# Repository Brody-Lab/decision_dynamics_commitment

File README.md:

# decision_dynamics_commitment
Code and data accompanying: Luo*, Kim*, et al. (2025). Transitions in dynamical regime and neural mode underlie perceptual decision-making. PMID: 37904994

The repository is organized into three main directories:

* `code/`: Analysis scripts and figure generation code, organized by figure.

* `data/`: Processed data files required to reproduce the analyses and figures, along with a link to the Dryad repository housing the raw data

* `figures/`: Editable vector graphics source files for the final figures.

Code and instructions for running the multi-mode drift-diffusion model (MMMDDM) can be found at https://github.com/Brody-Lab/fhmddm

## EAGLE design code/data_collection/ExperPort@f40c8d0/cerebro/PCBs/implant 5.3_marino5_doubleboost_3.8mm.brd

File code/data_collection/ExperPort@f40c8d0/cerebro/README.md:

# cerebro

Additional information and files can also be found in the Brody lab drive folder here https://drive.google.com/open?id=1JbdV_HZKmJ5FLsfGsrmhX1CqyznP0Qs2

Currently this lives in Research > Emily Dennis > cerebro

There's also a few spare files, especially the PCBs, that live in bucket in brodylab > cerebro

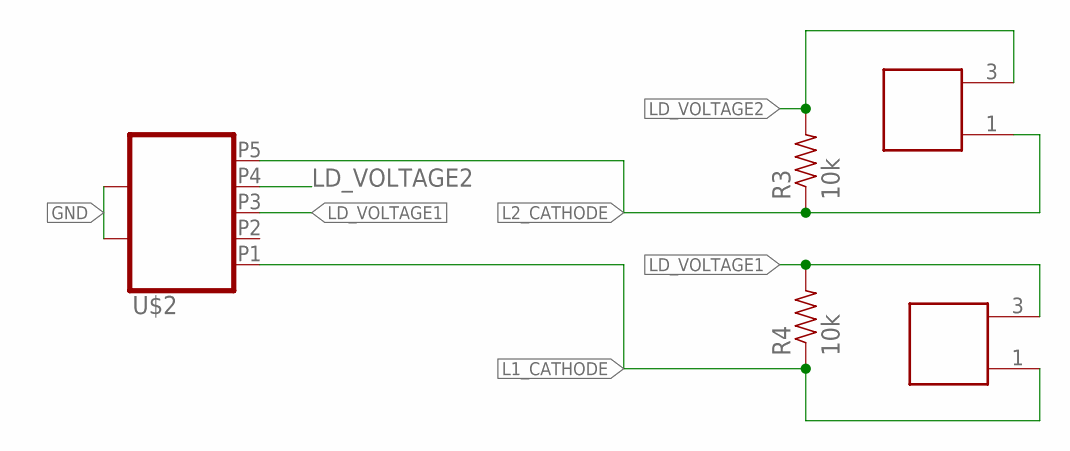
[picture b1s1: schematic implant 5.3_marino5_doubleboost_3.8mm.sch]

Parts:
R3, R4: 10k; 0805
U$2: USB_MICRO_SOCKET_VERT; USB_VERT_MICRO_SMD
U$4, U$5: TEST1; LASERDIODE_3.8_NEW

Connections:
GND: U$2.P$1, U$2.P$2, U$2.P$3
L1_CATHODE: R4.1, U$2.P1, U$5.1
L2_CATHODE: R3.1, U$2.P5, U$4.1
LD_VOLTAGE1: R4.2, U$2.P3, U$5.3
LD_VOLTAGE2: R3.2, U$2.P4, U$4.3

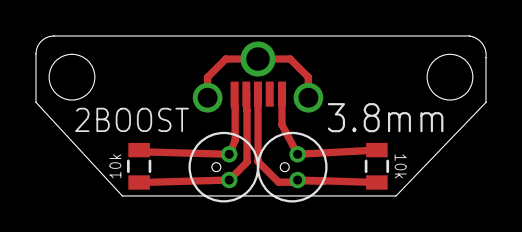
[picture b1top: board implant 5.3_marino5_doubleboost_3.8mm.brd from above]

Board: 2 copper layers, 25.0 x 8.9 mm, 5 parts (0 on the bottom side), 5 nets.

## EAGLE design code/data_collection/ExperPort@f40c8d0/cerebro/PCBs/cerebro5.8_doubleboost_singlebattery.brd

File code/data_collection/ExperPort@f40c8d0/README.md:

# ExperPort
All the code for BControl and running the Rodent Training Facility

# Setting up at home
The following are instructions for setting up at home. These are enough to start Dispatcher up, open a protocol, and be able to load and view data files.  They are not yet enough for being able to *run* and test a protocol at home. As of May 2022, these instructions work for Matlab 2022a.

1. Clone the https://github.com/Brody-Lab/ExperPort repository. 
* Note: cloning the repository to a folder in a mapped network drive, rather than to a folder in a local drive, may cause `bdata` to fail. 
3. To connect to `bdata` (one way to interact with the mySQL databases, and the way the rigs do it) you simply need to have the MySQLUtility subfolder in the ExperPort repo in your path and run `bdata_connect` to initialize the connection. This should be platform- and version-independent! If you do not intend to start Dispatcher or work with protocols and data/settings files you can stop here. Otherwise continue.
4. Clone the https://github.com/Brody-Lab/Protocols repository
5. Copy `ExperPort/Settings/Settings_Default.conf` to `ExperPort/Settings/Settings_Custom.conf`
6. In the new `Settings_Custom.conf`,
  * Edit this line to put in the path to your ExperPort directory, as in this example:
  * `GENERAL; Main_Code_Directory; /Users/carlos/Github/ExperPort`
  * Edit this line to put in the path to your SoloData directory, as in this example:
  * `GENERAL; Main_Code_Directory; /Users/carlos/Github/SoloData`
  * Edit this line to put in the path to the Protocols repository that sits outside ExperPort, as in this example:
  * `GENERAL; Protocols_Directory; ./Protocols:../Protocols`
  * Edit this line to tell it to use a local host sound server, as in this example:
  * `RIGS; sound_machine_server;     localhost;`
  * Edit this line, if needed, to make sure it says fake_rp-Box 3, for the Matlab emulator:
  * `RIGS; fake_rp_box;          3;`
1. Comment out these two lines in `mystartup.m`

   `% addpath([pwd filesep 'Protocols' filesep 'NewParamTester'])`
   
   `% addpath([pwd filesep 'Protocols' filesep 'SigmoidSamp7'])`
8. VPN into Princeton. If you forget to do this, Matlab will hang when trying to connext to bdata, and you might have to kill Matlab and start it again.
9. Start up Matlab, and change directory to wherever you cloned ExperPort
10. Run this within Matlab:  `addpath Protocols/; addpath MySQLUtility/ ; addpath Utility/ ; addpath Utility/Zut`
11. Run this within Matlab: `mystartup; newstartup; dispatcher init`
12. you're good to go, you can load a Protocol either through the menu on the Dispatcher window, or by running, in Matlab,
  `dispatcher set_protocol PROTOCOL_NAME` where `PROTOCOL_NAME` might be something like `PWM`, for example (no @ sign preceding it.
13. To load a data file after you've started a protocol, click on the green "Load Data" button in the protocol window. If needed, in the window that comes up, click on "options" at the bottom left, to ungray-out your data file and make it loadable.

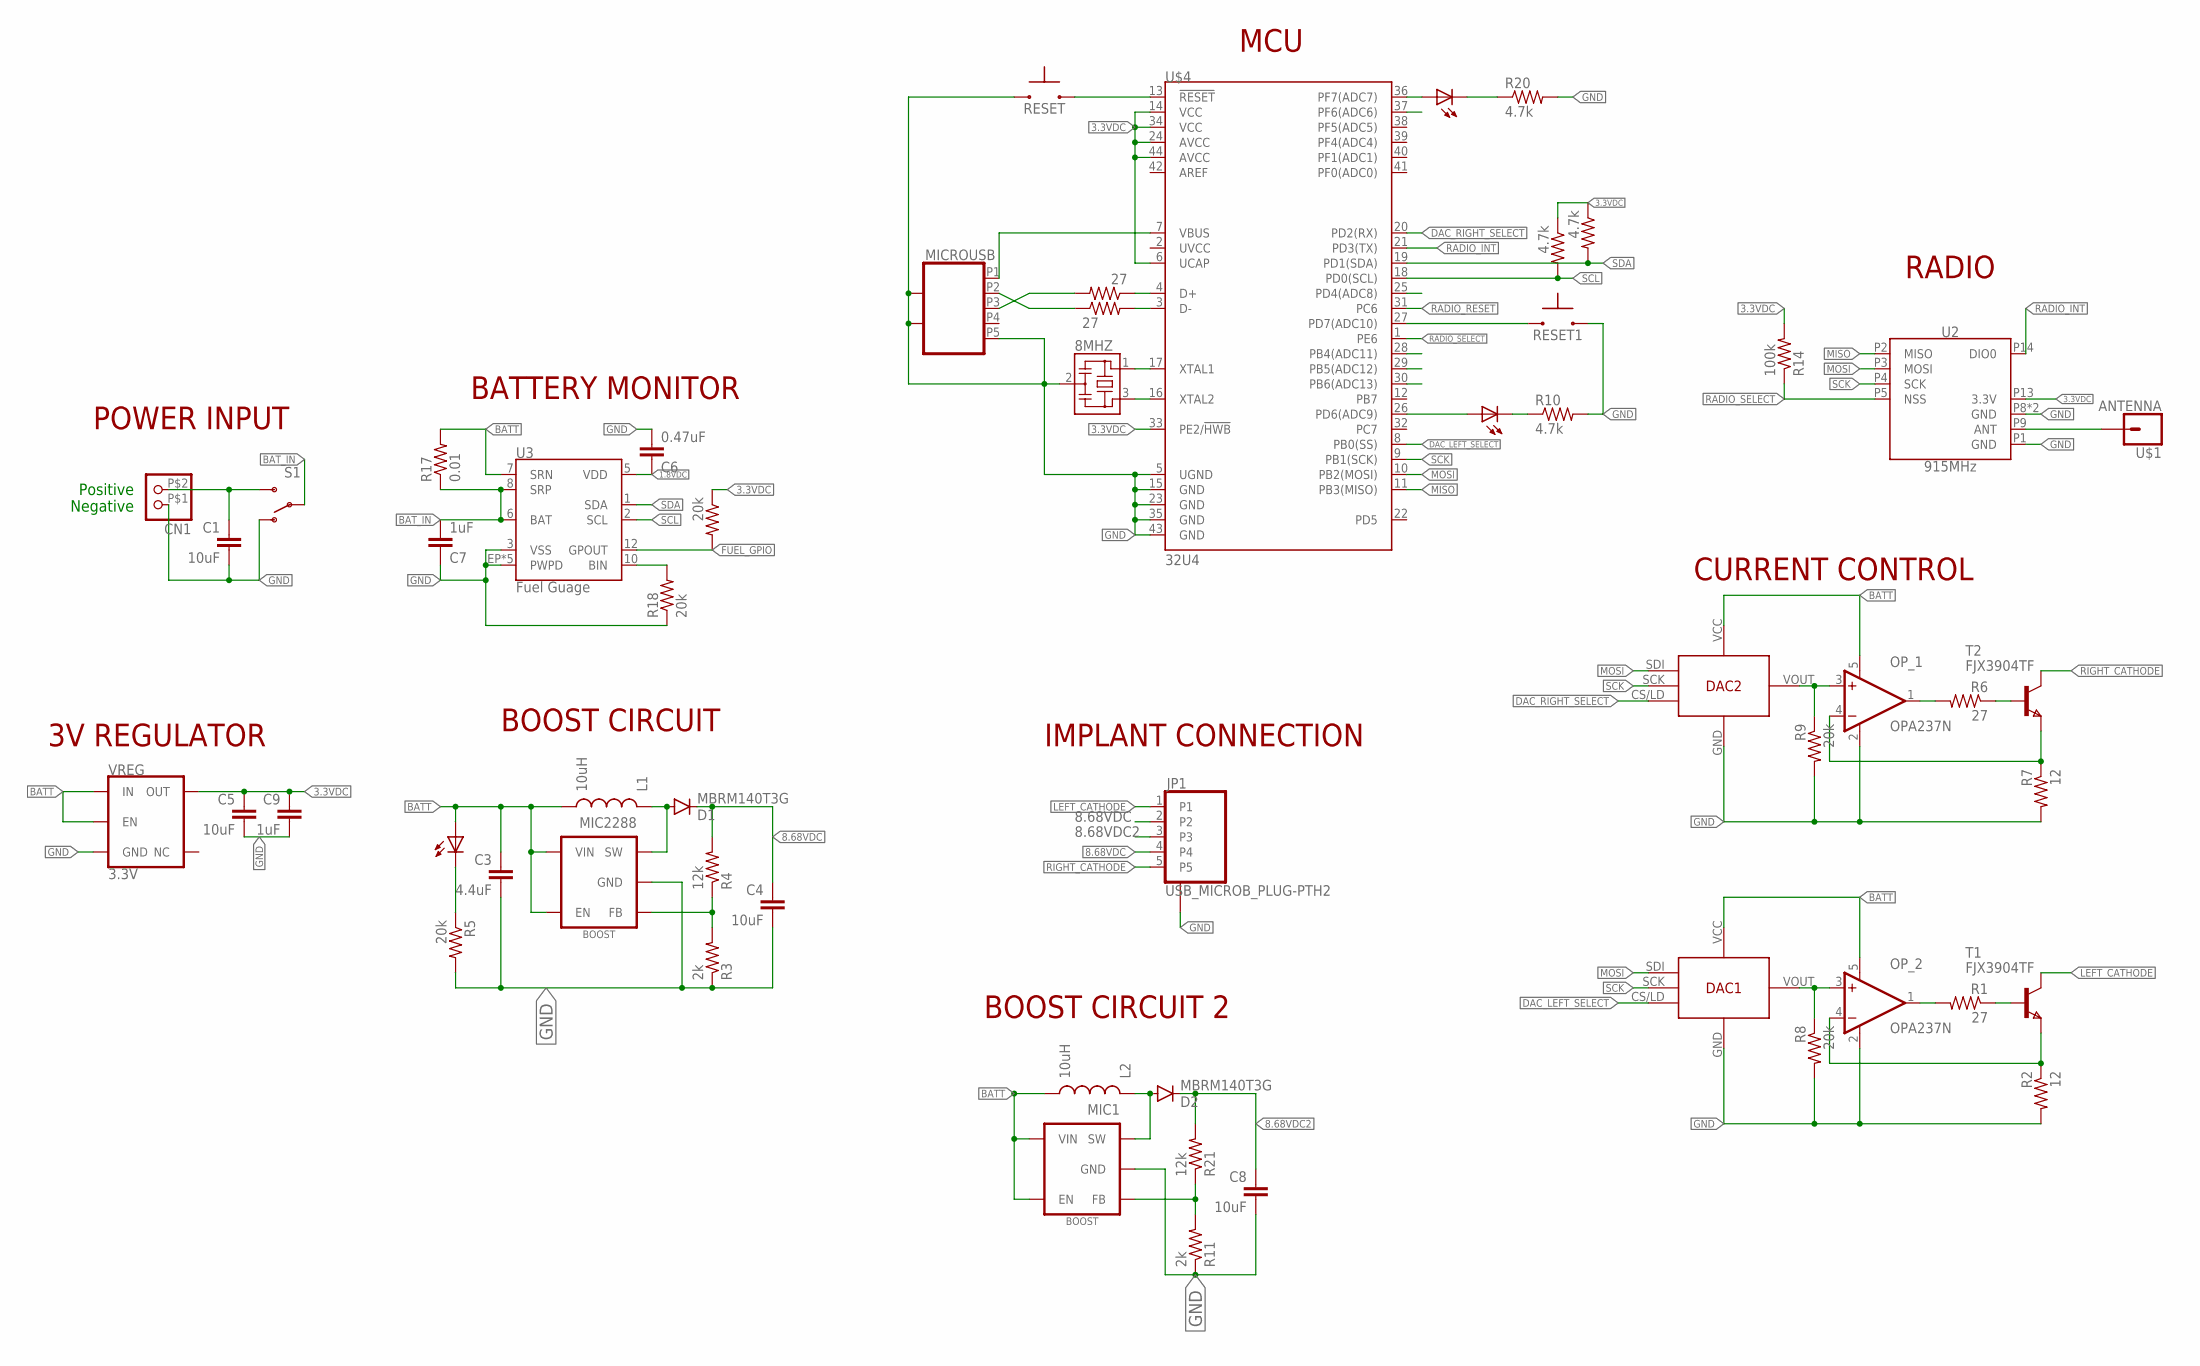
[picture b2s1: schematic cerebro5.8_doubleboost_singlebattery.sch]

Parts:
8MHZ: RESONATOR_CSTCE_V; CSTCE_V
C1, C4, C5, C8: 10uF; 0805
C3: 4.4uF; 0805
C6: 0.47uF; 0805
C7, C9: 1uF; 0805
CN1: JST_2PINMICRO; MICRO_LOCK_2PIN
D1, D2: MBRM140T3G; POWERMITE
DAC1, DAC2: DAC; SC-70
INDICATOR_LED: RED; CHIP-LED0603
INDICATOR_LED1: YLW; CHIP-LED0603
INDICATOR_LED2: GRN; CHIP-LED0603
JP1: USB_MICROB_PLUG-PTH2; MICRO-B-TH
L1, L2: 10uH; 1812
MIC1, MIC2288: BOOST; SOT23-5
MICROUSB: USB_MICRO_SOCKET_HORZ_REINFORCED; USB_HORZ_REINFORCED_MICRO
OP_1, OP_2: OPA237N; SOT23-5
R1, R6, R12, R13: 27; 0603-RES
R2, R7: 12; 0603-RES
R3, R11: 2k; 0603-RES
R4, R21: 12k; 0805
R5, R8, R9, R18, R19: 20k; 0603-RES
R10, R15, R16, R20: 4.7k; 0603-RES
R14: 100k; 0603-RES
R17: 0.01; 1206
RESET, RESET1: SWITCH-MOMENTARY-NO; SWITCH_MOMENTARY_XS
S1: SWITCH-SPDTREINFORCED_SMD; SWITCH-SPDT-SMD-REINFORCED
T1, T2: FJX3904TF; SOT323
U2: 915MHz; RFM69HCW-XXXS2
U3: Fuel Guage; PDSO-N12
U$1: ANTENNA; 1X01
U$4: 32U4; QFN-44-NOPAD
VREG: 3.3V; SOT23-5

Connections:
1.8VDC: C6.1, U3.5 (VDD)
3.3VDC: C5.1, C9.1, R14.2, R15.1, R16.1, R19.1, U2.P13 (3.3V), U$4.6 (UCAP), U$4.14 (VCC), U$4.24 (AVCC), U$4.33 (PE2/!HWB), U$4.34 (VCC), U$4.44 (AVCC), VREG.5 (OUT)
8.68VDC: C4.1, D1.CATHODE (C), JP1.2, JP1.4, R4.2
8.68VDC2: C8.1, D2.CATHODE (C), JP1.3, R21.2
BATT: C3.1, DAC1.VCC (VIN), DAC2.VCC (VIN), INDICATOR_LED.A, L1.P$2 (2), L1.P$4 (2), L2.P$2 (2), L2.P$4 (2), MIC1.4 (EN), MIC1.5 (VIN), MIC2288.4 (EN), MIC2288.5 (VIN), OP_1.5 (V+), OP_2.5 (V+), R17.2, U3.7 (SRN), VREG.1 (IN), VREG.3 (EN)
BAT_IN: C7.2, R17.1, S1.2, U3.6 (BAT), U3.8 (SRP)
DAC_LEFT_SELECT: DAC1.CS/LD, U$4.8 (PB0(SS))
DAC_RIGHT_SELECT: DAC2.CS/LD, U$4.20 (PD2(RX))
FUEL_GPIO: R19.2, U3.12 (GPOUT)
GND: 8MHZ.2, C1.2, C3.2, C4.2, C5.2, C6.2, C7.1, C8.2, C9.2, CN1.P$1 (1), DAC1.GND, DAC2.GND, JP1.P$1 (GND_PINS), JP1.P$2 (GND_PINS), MIC1.2 (GND), MIC2288.2 (GND), MICROUSB.G1, MICROUSB.G2, MICROUSB.P5, MICROUSB.P$1, MICROUSB.P$2, OP_1.2 (V-), OP_2.2 (V-), R2.2, R3.1, R5.2, R7.2, R8.2, R9.2, R10.2, R11.1, R18.1, R20.2, RESET.P$1 (1), RESET1.P$2 (2), S1.1 (O), U2.P1 (GND), U2.P8 (GND), U2.P10 (GND), U3.3 (VSS), U3.EP (PWPD), U3.EP1 (PWPD), U3.EP2 (PWPD), U3.EP3 (PWPD), U3.EP4 (PWPD), U$4.5 (UGND), U$4.15 (GND), U$4.23 (GND), U$4.35 (GND), U$4.43 (GND), VREG.2 (GND)
LEFT_CATHODE: JP1.1, T1.1 (C)
MISO: U2.P2 (MISO), U$4.11 (PB3(MISO))
MOSI: DAC1.SDI, DAC2.SDI, U2.P3 (MOSI), U$4.10 (PB2(MOSI))
unnamed: DAC2.VOUT, OP_1.3 (+IN), R9.1
unnamed: OP_1.4 (-IN), R7.1, T2.3 (E)
unnamed: DAC1.VOUT, OP_2.3 (+IN), R8.1
unnamed: C1.1, CN1.P$2 (2), S1.3 (S)
unnamed: OP_1.1 (OUT), R6.2
unnamed: OP_2.4 (-IN), R2.1, T1.3 (E)
unnamed: R6.1, T2.2 (B)
unnamed: INDICATOR_LED.C, R5.1
unnamed: OP_2.1 (OUT), R1.2
unnamed: MIC2288.3 (FB), R3.2, R4.1
unnamed: R1.1, T1.2 (B)
unnamed: 8MHZ.1, U$4.17 (XTAL1)
unnamed: 8MHZ.3, U$4.16 (XTAL2)
unnamed: MICROUSB.P1, U$4.7 (VBUS)
unnamed: D1.ANODE (A), L1.P$1 (1), L1.P$3 (1), MIC2288.1 (SW)
unnamed: R12.1, U$4.4 (D+)
unnamed: R13.2, U$4.3 (D-)
unnamed: MICROUSB.P3, R12.2
unnamed: MICROUSB.P2, R13.1
unnamed: INDICATOR_LED2.C, R10.1
unnamed: RESET1.P$1 (1), U$4.27 (PD7(ADC10))
unnamed: U2.P9 (ANT), U$1.1
unnamed: INDICATOR_LED1.C, R20.1
unnamed: INDICATOR_LED1.A, U$4.36 (PF7(ADC7))
unnamed: R18.2, U3.10 (BIN)
unnamed: INDICATOR_LED2.A, U$4.26 (PD6(ADC9))
unnamed: MIC1.3 (FB), R11.2, R21.1
unnamed: D2.ANODE (A), L2.P$1 (1), L2.P$3 (1), MIC1.1 (SW)
RADIO_INT: U2.P14 (DIO0), U$4.21 (PD3(TX))
RADIO_RESET: U$4.31 (PC6)
RADIO_SELECT: R14.1, U2.P5 (NSS), U$4.1 (PE6)
RESET: RESET.P$2 (2), U$4.13 (!RESET)
RIGHT_CATHODE: JP1.5, T2.1 (C)
SCK: DAC1.SCK, DAC2.SCK, U2.P4 (SCK), U$4.9 (PB1(SCK))
SCL: R15.2, U3.2 (SCL), U$4.18 (PD0(SCL))
SDA: R16.2, U3.1 (SDA), U$4.19 (PD1(SDA))

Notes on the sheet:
Positive
Negative
BOOST CIRCUIT
CURRENT CONTROL
RADIO
3V REGULATOR
BATTERY MONITOR
POWER INPUT
IMPLANT CONNECTION
MCU
BOOST CIRCUIT 2

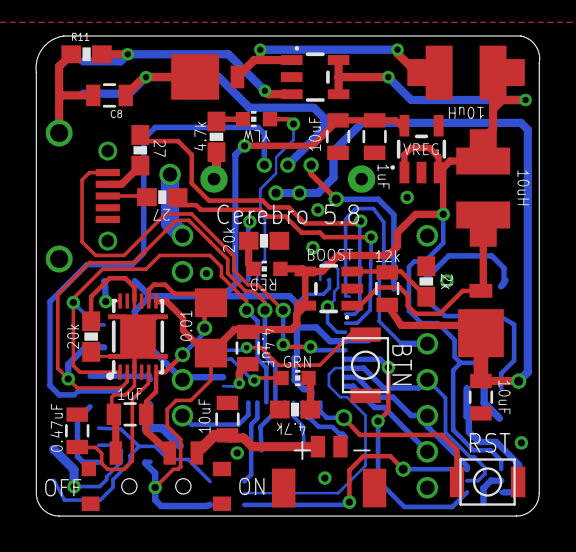
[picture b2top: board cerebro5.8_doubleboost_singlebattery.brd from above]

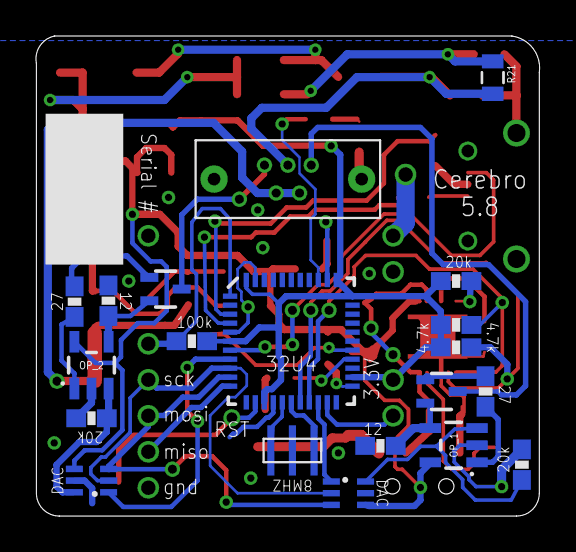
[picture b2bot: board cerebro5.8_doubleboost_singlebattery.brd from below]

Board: 2 copper layers, 28.0 x 26.7 mm, 56 parts (20 on the bottom side), 48 nets.

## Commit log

2025-04-25 gitignore
2025-04-25 initial
2025-04-26 fig1
2025-04-28 more scripts
2025-04-30 combine figures 4 & 5 into figure 6
2025-05-02 data update
2025-05-06 split figure 3 into figures 4 & 5
2025-05-06 table of nTc
2025-05-07 psychometrics in figure 5
2025-05-09 figure5
2025-05-13 add extended data figure 4
2025-05-13 add other extended data figures
2025-05-13 extended data figure 1
2025-05-13 code for figure 2 & edf 4a
2025-05-13 extended data figure 3
2025-05-13 move fig 2 data to edf 4
2025-05-13 rename edf 2 data
2025-05-14 extended data figure 4
2025-05-14 extended data figure 10a-c
2025-05-14 extended data figure 10d
2025-05-14 extended data figure 10e
2025-05-14 extended data figure 6h
2025-05-14 extended data figure 5b-d
2025-05-19 extended data figure 5e-g
2025-05-20 update to figure 3 and edf 5
2025-05-20 figure3
2025-05-30 add figure 3
2025-06-08 extended data figure 2
2025-06-13 update edf 10
2025-06-13 figure4
2025-06-13 added ExperPort and Protocols as submodules
2025-06-13 removed submodules
2025-06-13 added ExperPort and Protocols
2025-06-20 EDF 7
2025-07-01 figure6: minor
2025-08-18 edf 2: embed images
2025-12-22 nTc csv
2025-12-22 nTc spreadsheet documentation
2026-02-16 editted gitignore.txt
2026-02-16 docs: update MMDDM output download and path instructions
2026-02-16 Update figure5/panel_a.m to support MMDDM outputs
    Added check for external MMDDM data in data/MMDDM/.
    Maintained fallback to processed summary data for standard reproduction.
    Improved flexibility for users wishing to reproduce plots from raw model outputs.
